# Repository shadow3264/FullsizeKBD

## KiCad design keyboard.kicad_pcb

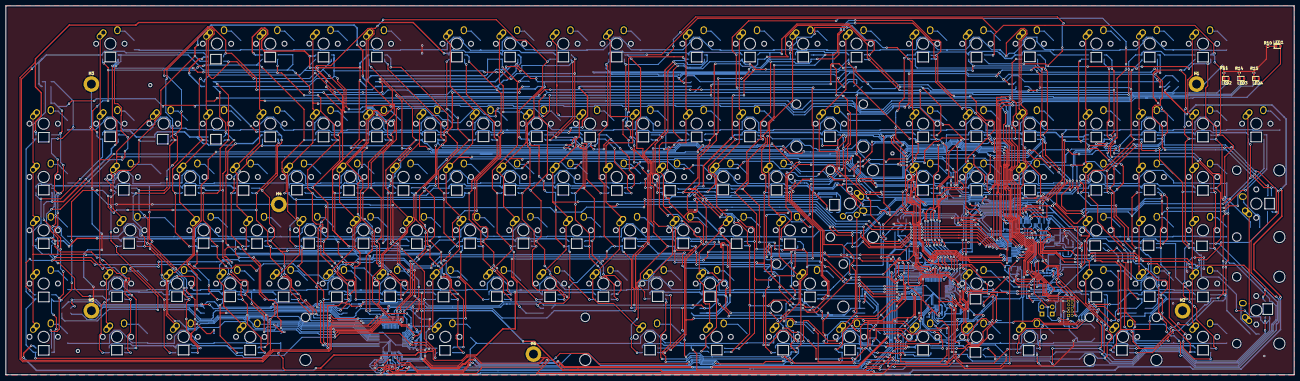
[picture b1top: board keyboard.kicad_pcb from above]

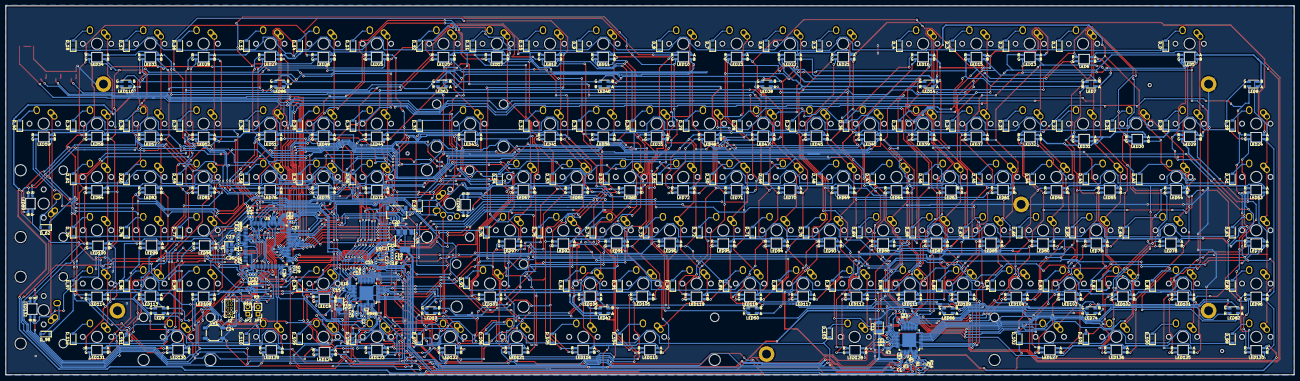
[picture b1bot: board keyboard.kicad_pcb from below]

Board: 2 copper layers, 460.4 x 131.8 mm, 434 parts (307 on the bottom side), 233 nets.

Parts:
C1, C2, C4, C6, C7, C9, C12, C15: 0.47uF; C_0402_1005Metric
C3, C5, C8, C10, C13, C16, C17, C18, C19, C21, C24, C28, C29, C30, C31, C32, C34, C38, C39, C40, C41, C42, C43, C44: 0.1uF; C_0402_1005Metric
C11, C14: 22uF; CP_EIA-3528-21_Kemet-B
C20, C27, C33: 1uF; C_0402_1005Metric
C23, C26: 12pF; C_0402_1005Metric
C25, C36, C37: 4.7uF; C_0402_1005Metric
C35: 10uF; C_0402_1005Metric
D_0, D_1, D_2, D_3, D_4, D_5, D_6, D_7, D_8, D_9, D_10, D_11, D_12, D_13, D_14, D_15, D_16, D_17, D_18, D_19, D_20, D_21, D_22, D_23, D_24, D_25, D_26, D_27, D_28, D_29, D_30, D_31, D_32, D_33, D_34, D_35, D_36, D_37, D_38, D_39, D_40, D_41, D_42, D_43, D_44, D_45, D_46, D_47, D_48, D_49, D_50, D_51, D_52, D_53, D_54, D_55, D_56, D_57, D_58, D_59, D_60, D_61, D_62, D_63, D_64, D_65, D_66, D_67, D_68, D_69, D_70, D_71, D_72, D_73, D_74, D_75, D_76, D_77, D_78, D_79, D_80, D_81, D_82, D_83, D_84, D_85, D_86, D_87, D_88, D_89, D_90, D_91, D_92, D_93, D_94, D_95, D_96, D_97, D_98, D_99, D_100, D_101, D_102, D_103, D_104, D_105, D_106, D_107, D_108, D_109, D_110, D_111, D_112: D; D_SOD-123
H1, H2, H3, H4, H5, H6: MountingHole_Pad; MountingHole_3.2mm_M3_DIN965_Pad
J1: USB; JST_SH_SM05B-SRSS-TB_1x05-1MP_P1.00mm_Horizontal
J2: Conn_02x05_Odd_Even; PinHeader_2x05_P1.27mm_Vertical
JP1, JP2: Jumper; PinHeader_1x02_P2.54mm_Vertical
K_0, K_1, K_2, K_3, K_4, K_5, K_6, K_7, K_8, K_9, K_10, K_11, K_12, K_13, K_14, K_15, K_16, K_17, K_18, K_19, K_20, K_21, K_22, K_23, K_24, K_25, K_26, K_27, K_28, K_29, K_30, K_31, K_32, K_34, K_35, K_36, K_37, K_38, K_39, K_40, K_41, K_43, K_44, K_45, K_46, K_47, K_48, K_49, K_50, K_51, K_52, K_53, K_54, K_56, K_57, K_58, K_59, K_60, K_61, K_63, K_65, K_66, K_67, K_68, K_69, K_70, K_71, K_72, K_73, K_74, K_75, K_76, K_77, K_78, K_79, K_80, K_82, K_83, K_84, K_85, K_86, K_87, K_88, K_89, K_90, K_91, K_92, K_94, K_95, K_96, K_97, K_99, K_108, K_109, K_110, K_112: KEYSW; MX-1U-NoLED
K_33, K_62, K_98, K_111: KEYSW; MX-2U-NoLED
K_42: KEYSW; MX-1.5U-NoLED
K_55: KEYSW; MX-ISO-NoLED
K_64: KEYSW; MX-1.75U-NoLED
K_81, K_100, K_101, K_102, K_104, K_105, K_106, K_107: KEYSW; MX-1.25U-NoLED
K_93: KEYSW; MX-2.75U-NoLED
K_103: KEYSW; MX-6.25U-NoLED
LED1, LED2, LED3, LED4: LED; LED_0603_1608Metric
LED5, LED6, LED10, LED11, LED12, LED13, LED15, LED16, LED17, LED18, LED20, LED21, LED22, LED23, LED24, LED25, LED26, LED27, LED28, LED29, LED30, LED31, LED32, LED33, LED34, LED35, LED36, LED37, LED39, LED40, LED41, LED43, LED44, LED45, LED47, LED48, LED49, LED51, LED52, LED53, LED54, LED55, LED56, LED57, LED58, LED59, LED60, LED61, LED63, LED64, LED65, LED67, LED68, LED69, LED70, LED71, LED72, LED73, LED75, LED76, LED77, LED78, LED79, LED80, LED81, LED83, LED84, LED85, LED87, LED88, LED89, LED90, LED91, LED92, LED93, LED94, LED95, LED96, LED97, LED98, LED99, LED100, LED101, LED102, LED103, LED104, LED105, LED106, LED107, LED108, LED109, LED111, LED112, LED113, LED114, LED115, LED116, LED117, LED118, LED119, LED120, LED121, LED122, LED123, LED124, LED125, LED126, LED127, LED128, LED129, LED130, LED131, LED132: RGBLED; LED_RGB_3.2x2.8_REVMOUNT
LED7, LED8, LED9, LED14, LED19, LED38, LED42, LED46, LED50, LED62, LED66, LED74, LED82, LED86, LED110: RGBLED; LED_RGB_3528
R1, R2, R16: 100k; R_0402_1005Metric
R3, R4: 20k; R_0402_1005Metric
R5, R6, R7, R8, R10, R11, R14, R15: 1k; R_0402_1005Metric
R9, R12: 10k; R_0402_1005Metric
R13: 220; R_0402_1005Metric
SW1: SW_Push; SW_SPST_SKQG_WithStem
U1, U2: IS31FL3733-TQ; TQFP-48-1EP_7x7mm_P0.5mm_EP5x5mm
U3: STM32F411VETx; LQFP-100_14x14mm_P0.5mm
U4: LD1117S50TR_SOT223; SOT-223-3_TabPin2
U5: MIC5504-3.3YM5; SOT-23-5
Y1: 16MHz; Crystal_SMD_3225-4Pin_3.2x2.5mm

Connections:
+3V3: C1.1, C2.2, C28.1, C29.1, C30.1, C31.1, C32.1, C33.1, C34.1, C35.1, C38.1, C39.1, C40.1, C41.1, C42.1, C43.1, C44.1, J2.1, JP1.2, JP2.2, R1.1, R5.1, R6.1, R7.1, R8.1, U1.39, U2.39, U3.6, U3.11, U3.19, U3.28, U3.50, U3.75, U3.100, U5.5
+5V: C3.1, C4.1, C5.1, C6.1, C7.1, C8.1, C9.1, C10.1, C11.1, C12.2, C13.2, C14.1, C15.2, C16.2, C17.1, C18.1, C19.1, C21.1, C25.1, C27.1, U1.20, U1.29, U1.37, U1.38, U2.20, U2.29, U2.37, U2.38, U4.2, U5.1, U5.3
/ledmatrix/LD1_CS1: LED5.1, LED6.1, LED7.1, LED8.1, U1.16
/ledmatrix/LD1_CS2: LED13.1, LED14.1, LED15.1, LED16.1, U1.17
/ledmatrix/LD1_CS3: LED21.1, LED22.1, LED23.1, LED24.1, U1.18
/ledmatrix/LD1_CS4: LED29.1, LED30.1, LED31.1, LED32.1, U1.19
/ledmatrix/LD1_CS5: LED37.1, LED38.1, LED39.1, LED40.1, U1.21
/ledmatrix/LD1_CS6: LED45.1, LED46.1, LED47.1, LED48.1, U1.22
/ledmatrix/LD1_CS7: LED53.1, LED54.1, LED55.1, LED56.1, U1.23
/ledmatrix/LD1_CS8: LED61.1, LED62.1, LED63.1, LED64.1, U1.24
/ledmatrix/LD1_CS9: LED69.1, LED70.1, LED71.1, LED72.1, U1.25
/ledmatrix/LD1_CS10: LED77.1, LED78.1, LED79.1, LED80.1, U1.26
/ledmatrix/LD1_CS11: LED85.1, LED86.1, LED87.1, LED88.1, U1.27
/ledmatrix/LD1_CS12: LED93.1, LED94.1, LED95.1, LED96.1, U1.28
/ledmatrix/LD1_CS13: LED101.1, LED102.1, LED103.1, LED104.1, U1.30
/ledmatrix/LD1_CS14: LED109.1, LED110.1, LED111.1, LED112.1, U1.31
/ledmatrix/LD1_CS15: LED117.1, LED118.1, LED119.1, LED120.1, U1.32
/ledmatrix/LD1_CS16: LED125.1, LED126.1, LED127.1, LED128.1, U1.33
/ledmatrix/LD1_SW1: LED5.3, LED13.3, LED21.3, LED29.3, LED37.3, LED45.3, LED53.3, LED61.3, LED69.3, LED77.3, LED85.3, LED93.3, LED101.3, LED109.3, LED117.3, LED125.3, U1.2
/ledmatrix/LD1_SW2: LED5.2, LED13.2, LED21.2, LED29.2, LED37.2, LED45.2, LED53.2, LED61.2, LED69.2, LED77.2, LED85.2, LED93.2, LED101.2, LED109.2, LED117.2, LED125.2, U1.3
/ledmatrix/LD1_SW3: LED5.4, LED13.4, LED21.4, LED29.4, LED37.4, LED45.4, LED53.4, LED61.4, LED69.4, LED77.4, LED85.4, LED93.4, LED101.4, LED109.4, LED117.4, LED125.4, U1.4
/ledmatrix/LD1_SW4: LED6.3, LED14.3, LED22.3, LED30.3, LED38.3, LED46.3, LED54.3, LED62.3, LED70.3, LED78.3, LED86.3, LED94.3, LED102.3, LED110.3, LED118.3, LED126.3, U1.6
/ledmatrix/LD1_SW5: LED6.2, LED14.2, LED22.2, LED30.2, LED38.2, LED46.2, LED54.2, LED62.2, LED70.2, LED78.2, LED86.2, LED94.2, LED102.2, LED110.2, LED118.2, LED126.2, U1.7
/ledmatrix/LD1_SW6: LED6.4, LED14.4, LED22.4, LED30.4, LED38.4, LED46.4, LED54.4, LED62.4, LED70.4, LED78.4, LED86.4, LED94.4, LED102.4, LED110.4, LED118.4, LED126.4, U1.8
/ledmatrix/LD1_SW7: LED7.3, LED15.3, LED23.3, LED31.3, LED39.3, LED47.3, LED55.3, LED63.3, LED71.3, LED79.3, LED87.3, LED95.3, LED103.3, LED111.3, LED119.3, LED127.3, U1.9
/ledmatrix/LD1_SW8: LED7.2, LED15.2, LED23.2, LED31.2, LED39.2, LED47.2, LED55.2, LED63.2, LED71.2, LED79.2, LED87.2, LED95.2, LED103.2, LED111.2, LED119.2, LED127.2, U1.10
/ledmatrix/LD1_SW9: LED7.4, LED15.4, LED23.4, LED31.4, LED39.4, LED47.4, LED55.4, LED63.4, LED71.4, LED79.4, LED87.4, LED95.4, LED103.4, LED111.4, LED119.4, LED127.4, U1.11
/ledmatrix/LD1_SW10: LED8.3, LED16.3, LED24.3, LED32.3, LED40.3, LED48.3, LED56.3, LED64.3, LED72.3, LED80.3, LED88.3, LED96.3, LED104.3, LED112.3, LED120.3, LED128.3, U1.13
/ledmatrix/LD1_SW11: LED8.2, LED16.2, LED24.2, LED32.2, LED40.2, LED48.2, LED56.2, LED64.2, LED72.2, LED80.2, LED88.2, LED96.2, LED104.2, LED112.2, LED120.2, LED128.2, U1.14
/ledmatrix/LD1_SW12: LED8.4, LED16.4, LED24.4, LED32.4, LED40.4, LED48.4, LED56.4, LED64.4, LED72.4, LED80.4, LED88.4, LED96.4, LED104.4, LED112.4, LED120.4, LED128.4, U1.15
/ledmatrix/LD2_CS1: LED9.1, LED10.1, LED11.1, LED12.1, U2.16
/ledmatrix/LD2_CS2: LED17.1, LED18.1, LED19.1, LED20.1, U2.17
/ledmatrix/LD2_CS3: LED25.1, LED26.1, LED27.1, LED28.1, U2.18
/ledmatrix/LD2_CS4: LED33.1, LED34.1, LED35.1, LED36.1, U2.19
/ledmatrix/LD2_CS5: LED41.1, LED42.1, LED43.1, LED44.1, U2.21
/ledmatrix/LD2_CS6: LED49.1, LED50.1, LED51.1, LED52.1, U2.22
/ledmatrix/LD2_CS7: LED57.1, LED58.1, LED59.1, LED60.1, U2.23
/ledmatrix/LD2_CS8: LED65.1, LED66.1, LED67.1, LED68.1, U2.24
/ledmatrix/LD2_CS9: LED73.1, LED74.1, LED75.1, LED76.1, U2.25
/ledmatrix/LD2_CS10: LED81.1, LED82.1, LED83.1, LED84.1, U2.26
/ledmatrix/LD2_CS11: LED89.1, LED90.1, LED91.1, LED92.1, U2.27
/ledmatrix/LD2_CS12: LED97.1, LED98.1, LED99.1, LED100.1, U2.28
/ledmatrix/LD2_CS13: LED105.1, LED106.1, LED107.1, LED108.1, U2.30
/ledmatrix/LD2_CS14: LED113.1, LED114.1, LED115.1, LED116.1, U2.31
/ledmatrix/LD2_CS15: LED121.1, LED122.1, LED123.1, LED124.1, U2.32
/ledmatrix/LD2_CS16: LED129.1, LED130.1, LED131.1, LED132.1, U2.33
/ledmatrix/LD2_SW1: LED9.3, LED17.3, LED25.3, LED33.3, LED41.3, LED49.3, LED57.3, LED65.3, LED73.3, LED81.3, LED89.3, LED97.3, LED105.3, LED113.3, LED121.3, LED129.3, U2.2
/ledmatrix/LD2_SW2: LED9.2, LED17.2, LED25.2, LED33.2, LED41.2, LED49.2, LED57.2, LED65.2, LED73.2, LED81.2, LED89.2, LED97.2, LED105.2, LED113.2, LED121.2, LED129.2, U2.3
/ledmatrix/LD2_SW3: LED9.4, LED17.4, LED25.4, LED33.4, LED41.4, LED49.4, LED57.4, LED65.4, LED73.4, LED81.4, LED89.4, LED97.4, LED105.4, LED113.4, LED121.4, LED129.4, U2.4
/ledmatrix/LD2_SW4: LED10.3, LED18.3, LED26.3, LED34.3, LED42.3, LED50.3, LED58.3, LED66.3, LED74.3, LED82.3, LED90.3, LED98.3, LED106.3, LED114.3, LED122.3, LED130.3, U2.6
/ledmatrix/LD2_SW5: LED10.2, LED18.2, LED26.2, LED34.2, LED42.2, LED50.2, LED58.2, LED66.2, LED74.2, LED82.2, LED90.2, LED98.2, LED106.2, LED114.2, LED122.2, LED130.2, U2.7
/ledmatrix/LD2_SW6: LED10.4, LED18.4, LED26.4, LED34.4, LED42.4, LED50.4, LED58.4, LED66.4, LED74.4, LED82.4, LED90.4, LED98.4, LED106.4, LED114.4, LED122.4, LED130.4, U2.8
/ledmatrix/LD2_SW7: LED11.3, LED19.3, LED27.3, LED35.3, LED43.3, LED51.3, LED59.3, LED67.3, LED75.3, LED83.3, LED91.3, LED99.3, LED107.3, LED115.3, LED123.3, LED131.3, U2.9
/ledmatrix/LD2_SW8: LED11.2, LED19.2, LED27.2, LED35.2, LED43.2, LED51.2, LED59.2, LED67.2, LED75.2, LED83.2, LED91.2, LED99.2, LED107.2, LED115.2, LED123.2, LED131.2, U2.10
/ledmatrix/LD2_SW9: LED11.4, LED19.4, LED27.4, LED35.4, LED43.4, LED51.4, LED59.4, LED67.4, LED75.4, LED83.4, LED91.4, LED99.4, LED107.4, LED115.4, LED123.4, LED131.4, U2.11
/ledmatrix/LD2_SW10: LED12.3, LED20.3, LED28.3, LED36.3, LED44.3, LED52.3, LED60.3, LED68.3, LED76.3, LED84.3, LED92.3, LED100.3, LED108.3, LED116.3, LED124.3, LED132.3, U2.13
/ledmatrix/LD2_SW11: LED12.2, LED20.2, LED28.2, LED36.2, LED44.2, LED52.2, LED60.2, LED68.2, LED76.2, LED84.2, LED92.2, LED100.2, LED108.2, LED116.2, LED124.2, LED132.2, U2.14
/ledmatrix/LD2_SW12: LED12.4, LED20.4, LED28.4, LED36.4, LED44.4, LED52.4, LED60.4, LED68.4, LED76.4, LED84.4, LED92.4, LED100.4, LED108.4, LED116.4, LED124.4, LED132.4, U2.15
/mcu/SYNC: U1.40, U2.40
BOOT0: JP1.1, R9.2, U3.94
BOOT1: JP2.1, R12.2, U3.37
GND: C1.2, C2.1, C3.2, C4.2, C5.2, C6.2, C7.2, C8.2, C9.2, C10.2, C11.2, C12.1, C13.1, C14.2, C15.1, C16.1, C17.2, C18.2, C19.2, C20.2, C21.2, C23.2, C24.2, C25.2, C26.2, C27.2, C28.2, C29.2, C30.2, C31.2, C32.2, C33.2, C34.2, C35.2, C36.2, C37.2, C38.2, C39.2, C40.2, C41.2, C42.2, C43.2, C44.2, H1.1, H2.1, H3.1, H4.1, H5.1, H6.1, J1.1, J2.3, J2.5, J2.9, R2.2, R3.2, R4.2, R9.1, R10.1, R11.1, R12.1, R14.1, R15.1, R16.2, SW1.2, U1.5, U1.12, U1.34, U1.43, U1.44, U1.48, U1.49, U2.5, U2.12, U2.34, U2.43, U2.44, U2.48, U2.49, U3.10, U3.20, U3.27, U3.49, U3.74, U3.99, U4.1, U5.2, Y1.2, Y1.4
HSE_IN: C23.1, U3.12, Y1.1
HSE_OUT: R13.1, U3.13
I2C1_SCL: R5.2, U1.42, U3.92
I2C1_SDA: R7.2, U1.41, U3.93
I2C2_SCL: R6.2, U2.42, U3.47
I2C2_SDA: R8.2, U2.41, U3.96
IICRST: R16.1, U1.47, U2.47
INTB: R1.2, U1.45
NRST: C24.1, J2.10, SW1.1, U3.14
unnamed: C26.1, R13.2, Y1.3
unnamed: C36.1, U3.48
unnamed: C37.1, U3.73
unnamed: D_0.2, K_0.2
unnamed: D_1.2, K_1.2
unnamed: D_2.2, K_2.2
unnamed: D_3.2, K_3.2
unnamed: D_4.2, K_4.2
unnamed: D_5.2, K_5.2
unnamed: D_6.2, K_6.2
unnamed: D_7.2, K_7.2
unnamed: D_8.2, K_8.2
unnamed: D_9.2, K_9.2
unnamed: D_10.2, K_10.2
unnamed: D_11.2, K_11.2
unnamed: D_12.2, K_12.2
unnamed: D_13.2, K_13.2
unnamed: D_14.2, K_14.2
unnamed: D_15.2, K_15.2
unnamed: D_16.2, K_16.2
unnamed: D_17.2, K_17.2
unnamed: D_18.2, K_18.2
unnamed: D_19.2, K_19.2
unnamed: D_20.2, K_20.2
unnamed: D_21.2, K_21.2
unnamed: D_22.2, K_22.2
unnamed: D_23.2, K_23.2
unnamed: D_24.2, K_24.2
unnamed: D_25.2, K_25.2
unnamed: D_26.2, K_26.2
unnamed: D_27.2, K_27.2
unnamed: D_28.2, K_28.2
unnamed: D_29.2, K_29.2
unnamed: D_30.2, K_30.2
unnamed: D_31.2, K_31.2
unnamed: D_32.2, K_32.2
unnamed: D_33.2, K_33.2
unnamed: D_34.2, K_34.2
unnamed: D_35.2, K_35.2
unnamed: D_36.2, K_36.2
unnamed: D_37.2, K_37.2
unnamed: D_38.2, K_38.2
unnamed: D_39.2, K_39.2
unnamed: D_40.2, K_40.2
unnamed: D_41.2, K_41.2
unnamed: D_42.2, K_42.2
unnamed: D_43.2, K_43.2
unnamed: D_44.2, K_44.2
unnamed: D_45.2, K_45.2
unnamed: D_46.2, K_46.2
unnamed: D_47.2, K_47.2
unnamed: D_48.2, K_48.2
unnamed: D_49.2, K_49.2
unnamed: D_50.2, K_50.2
unnamed: D_51.2, K_51.2
unnamed: D_52.2, K_52.2
unnamed: D_53.2, K_53.2
unnamed: D_54.2, K_54.2
unnamed: D_55.2, K_55.2
unnamed: D_56.2, K_56.2
unnamed: D_57.2, K_57.2
unnamed: D_58.2, K_58.2
unnamed: D_59.2, K_59.2
unnamed: D_60.2, K_60.2
unnamed: D_61.2, K_61.2
unnamed: D_62.2, K_62.2
unnamed: D_63.2, K_63.2
unnamed: D_64.2, K_64.2
unnamed: D_65.2, K_65.2
unnamed: D_66.2, K_66.2
unnamed: D_67.2, K_67.2
unnamed: D_68.2, K_68.2
unnamed: D_69.2, K_69.2
unnamed: D_70.2, K_70.2
unnamed: D_71.2, K_71.2
unnamed: D_72.2, K_72.2
unnamed: D_73.2, K_73.2
unnamed: D_74.2, K_74.2
unnamed: D_75.2, K_75.2
unnamed: D_76.2, K_76.2
unnamed: D_77.2, K_77.2
unnamed: D_78.2, K_78.2
unnamed: D_79.2, K_79.2
unnamed: D_80.2, K_80.2
unnamed: D_81.2, K_81.2
unnamed: D_82.2, K_82.2
unnamed: D_83.2, K_83.2
unnamed: D_84.2, K_84.2
unnamed: D_85.2, K_85.2
unnamed: D_86.2, K_86.2
unnamed: D_87.2, K_87.2
unnamed: D_88.2, K_88.2
unnamed: D_89.2, K_89.2
unnamed: D_90.2, K_90.2
unnamed: D_91.2, K_91.2
unnamed: D_92.2, K_92.2
unnamed: D_93.2, K_93.2
unnamed: D_94.2, K_94.2
unnamed: D_95.2, K_95.2
unnamed: D_96.2, K_96.2
unnamed: D_97.2, K_97.2
unnamed: D_98.2, K_98.2
unnamed: D_99.2, K_99.2
unnamed: D_100.2, K_100.2
unnamed: D_101.2, K_101.2
unnamed: D_102.2, K_102.2
unnamed: D_103.2, K_103.2
unnamed: D_104.2, K_104.2
unnamed: D_105.2, K_105.2
unnamed: D_106.2, K_106.2
unnamed: D_107.2, K_107.2
unnamed: D_108.2, K_108.2
unnamed: D_109.2, K_109.2
unnamed: D_110.2, K_110.2
unnamed: D_111.2, K_111.2
unnamed: D_112.2, K_112.2
unnamed: LED1.1, R10.2
unnamed: LED2.1, R11.2
unnamed: LED3.1, R14.2
unnamed: LED4.1, R15.2
unnamed: R3.1, U1.35
unnamed: R4.1, U2.35
PA8: LED2.2, U3.67
PA9: LED3.2, U3.68
PA10: LED4.2, U3.69
PB12: LED1.2, U3.51
SDB: R2.1, U1.46, U2.46, U3.81
SWCLK: J2.4, U3.76
SWDIO: J2.2, U3.72
SWO: J2.6, U3.89
USB_DM: J1.3, U3.70
USB_DP: J1.2, U3.71
VBUS: C20.1, J1.4, U4.3
col0: K_19.1, K_41.1, K_63.1, K_80.1, K_99.1, U3.52
col1: K_0.1, K_20.1, K_81.1, K_100.1, U3.53
col2: K_21.1, K_42.1, K_64.1, U3.54
col3: K_1.1, K_22.1, K_43.1, K_65.1, K_82.1, K_101.1, U3.55
col4: K_2.1, K_23.1, K_44.1, K_66.1, K_83.1, K_102.1, U3.56
col5: K_3.1, K_24.1, K_45.1, K_67.1, K_84.1, U3.57
col6: K_4.1, K_25.1, K_46.1, K_68.1, K_85.1, U3.58
col7: K_26.1, K_47.1, K_69.1, K_86.1, U3.59
col8: K_5.1, K_27.1, K_48.1, K_70.1, K_87.1, K_103.1, U3.60
col9: K_6.1, K_28.1, K_49.1, K_71.1, K_88.1, U3.61
col10: K_7.1, K_29.1, K_50.1, K_72.1, K_89.1, U3.62
col11: K_8.1, K_30.1, K_51.1, K_73.1, K_90.1, K_104.1, U3.63
col12: K_9.1, K_31.1, K_52.1, K_74.1, K_91.1, U3.64
col13: K_10.1, K_32.1, K_53.1, K_75.1, K_92.1, K_105.1, U3.65
col14: K_11.1, K_54.1, K_76.1, K_93.1, K_106.1, U3.66
col15: K_12.1, K_33.1, K_55.1, K_107.1, U3.78
col16: K_13.1, K_34.1, K_56.1, K_108.1, U3.79
col17: K_14.1, K_35.1, K_57.1, K_94.1, K_109.1, U3.80
col18: K_15.1, K_36.1, K_58.1, K_110.1, U3.7
col19: K_16.1, K_37.1, K_59.1, K_77.1, K_95.1, K_111.1, U3.8
col20: K_17.1, K_38.1, K_60.1, K_78.1, K_96.1, U3.9
col21: K_18.1, K_39.1, K_61.1, K_79.1, K_97.1, K_112.1, U3.90
col22: K_40.1, K_62.1, K_98.1, U3.91
row0: D_0.1, D_1.1, D_2.1, D_3.1, D_4.1, D_5.1, D_6.1, D_7.1, D_8.1, D_9.1, D_10.1, D_11.1, D_12.1, D_13.1, D_14.1, D_15.1, D_16.1, D_17.1, D_18.1, U3.82
row1: D_19.1, D_20.1, D_21.1, D_22.1, D_23.1, D_24.1, D_25.1, D_26.1, D_27.1, D_28.1, D_29.1, D_30.1, D_31.1, D_32.1, D_33.1, D_34.1, D_35.1, D_36.1, D_37.1, D_38.1, D_39.1, D_40.1, U3.83
row2: D_41.1, D_42.1, D_43.1, D_44.1, D_45.1, D_46.1, D_47.1, D_48.1, D_49.1, D_50.1, D_51.1, D_52.1, D_53.1, D_54.1, D_55.1, D_56.1, D_57.1, D_58.1, D_59.1, D_60.1, D_61.1, D_62.1, U3.84
row3: D_63.1, D_64.1, D_65.1, D_66.1, D_67.1, D_68.1, D_69.1, D_70.1, D_71.1, D_72.1, D_73.1, D_74.1, D_75.1, D_76.1, D_77.1, D_78.1, D_79.1, U3.85
row4: D_80.1, D_81.1, D_82.1, D_83.1, D_84.1, D_85.1, D_86.1, D_87.1, D_88.1, D_89.1, D_90.1, D_91.1, D_92.1, D_93.1, D_94.1, D_95.1, D_96.1, D_97.1, D_98.1, U3.86
row5: D_99.1, D_100.1, D_101.1, D_102.1, D_103.1, D_104.1, D_105.1, D_106.1, D_107.1, D_108.1, D_109.1, D_110.1, D_111.1, D_112.1, U3.87

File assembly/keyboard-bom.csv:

Comment,Designator,Footprint,LCSC
"22uF","C11,C14","Capacitor_Tantalum_SMD:CP_EIA-3528-21_Kemet-B","C129568"
"0.1uF","C3,C5,C8,C10,C13,C16,C17,C18,C19,C21,C24,C28,C29,C30,C31,C32,C34,C38,C39,C40,C41,C42,C43,C44","Capacitor_SMD:C_0402_1005Metric","C1525"
"4.7uF","C25,C36,C37","Capacitor_SMD:C_0402_1005Metric","C47339"
"12pF","C23,C26","Capacitor_SMD:C_0402_1005Metric","C1547"
"1uF","C20,C27,C33","Capacitor_SMD:C_0402_1005Metric","C52923"
"10uF","C35","Capacitor_SMD:C_0402_1005Metric","C15525"
"0.47uF","C1,C2,C4,C6,C7,C9,C12,C15","Capacitor_SMD:C_0402_1005Metric","C32949"
"D","D_0,D_1,D_2,D_3,D_4,D_5,D_6,D_7,D_8,D_9,D_10,D_11,D_12,D_13,D_14,D_15,D_16,D_17,D_18,D_19,D_20,D_21,D_22,D_23,D_24,D_25,D_26,D_27,D_28,D_29,D_30,D_31,D_32,D_33,D_34,D_35,D_36,D_37,D_38,D_39,D_40,D_41,D_42,D_43,D_44,D_45,D_46,D_47,D_48,D_49,D_50,D_51,D_52,D_53,D_54,D_55,D_56,D_57,D_58,D_59,D_60,D_61,D_62,D_63,D_64,D_65,D_66,D_67,D_68,D_69,D_70,D_71,D_72,D_73,D_74,D_75,D_76,D_77,D_78,D_79,D_80,D_81,D_82,D_83,D_84,D_85,D_86,D_87,D_88,D_89,D_90,D_91,D_92,D_93,D_94,D_95,D_96,D_97,D_98,D_99,D_100,D_101,D_102,D_103,D_104,D_105,D_106,D_107,D_108,D_109,D_110,D_111,D_112","Diode_SMD:D_SOD-123","C81598"
"MountingHole_Pad","H1,H2,H3,H4,H5,H6","MountingHole:MountingHole_3.2mm_M3_DIN965_Pad",""
"USB","J1","Connector_JST:JST_SH_SM05B-SRSS-TB_1x05-1MP_P1.00mm_Horizontal","C265104"
"Conn_02x05_Odd_Even","J2","Connector_PinHeader_1.27mm:PinHeader_2x05_P1.27mm_Vertical",""
"Jumper","JP1,JP2","Connector_PinHeader_2.54mm:PinHeader_1x02_P2.54mm_Vertical",""
"KEYSW","K_0,K_1,K_2,K_3,K_4,K_5,K_6,K_7,K_8,K_9,K_10,K_11,K_12,K_13,K_14,K_15,K_16,K_17,K_18,K_19,K_20,K_21,K_22,K_23,K_24,K_25,K_26,K_27,K_28,K_29,K_30,K_31,K_32,K_34,K_35,K_36,K_37,K_38,K_39,K_40,K_41,K_43,K_44,K_45,K_46,K_47,K_48,K_49,K_50,K_51,K_52,K_53,K_54,K_56,K_57,K_58,K_59,K_60,K_61,K_63,K_65,K_66,K_67,K_68,K_69,K_70,K_71,K_72,K_73,K_74,K_75,K_76,K_77,K_78,K_79,K_80,K_82,K_83,K_84,K_85,K_86,K_87,K_88,K_89,K_90,K_91,K_92,K_94,K_95,K_96,K_97,K_99,K_108,K_109,K_110,K_112","MX_Alps_Hybrid:MX-1U-NoLED",""
"KEYSW","K_103","MX_Alps_Hybrid:MX-6.25U-NoLED",""
"KEYSW","K_33,K_62,K_98,K_111","MX_Alps_Hybrid:MX-2U-NoLED",""
"KEYSW","K_42","MX_Alps_Hybrid:MX-1.5U-NoLED",""
"KEYSW","K_55","FullsizeKBD:MX-ISO-NoLED",""
"KEYSW","K_64","MX_Alps_Hybrid:MX-1.75U-NoLED",""
"KEYSW","K_81,K_100,K_101,K_102,K_104,K_105,K_106,K_107","MX_Alps_Hybrid:MX-1.25U-NoLED",""
"KEYSW","K_93","MX_Alps_Hybrid:MX-2.75U-NoLED",""
"LED","LED1,LED2,LED3,LED4","LED_SMD:LED_0603_1608Metric","C84269"
"RGBLED","LED5,LED6,LED10,LED11,LED12,LED13,LED15,LED16,LED17,LED18,LED20,LED21,LED22,LED23,LED24,LED25,LED26,LED27,LED28,LED29,LED30,LED31,LED32,LED33,LED34,LED35,LED36,LED37,LED39,LED40,LED41,LED43,LED44,LED45,LED47,LED48,LED49,LED51,LED52,LED53,LED54,LED55,LED56,LED57,LED58,LED59,LED60,LED61,LED63,LED64,LED65,LED67,LED68,LED69,LED70,LED71,LED72,LED73,LED75,LED76,LED77,LED78,LED79,LED80,LED81,LED83,LED84,LED85,LED87,LED88,LED89,LED90,LED91,LED92,LED93,LED94,LED95,LED96,LED97,LED98,LED99,LED100,LED101,LED102,LED103,LED104,LED105,LED106,LED107,LED108,LED109,LED111,LED112,LED113,LED114,LED115,LED116,LED117,LED118,LED119,LED120,LED121,LED122,LED123,LED124,LED125,LED126,LED127,LED128,LED129,LED130,LED131,LED132","FullsizeKBD:LED_RGB_3.2x2.8_REVMOUNT",""
"RGBLED","LED7,LED8,LED9,LED14,LED19,LED38,LED42,LED46,LED50,LED62,LED66,LED74,LED82,LED86,LED110","FullsizeKBD:LED_RGB_3528",""
"100k","R1,R2,R16","Resistor_SMD:R_0402_1005Metric","C25741"
"1k","R5,R6,R7,R8,R10,R11,R14,R15","Resistor_SMD:R_0402_1005Metric","C11702"
"220","R13","Resistor_SMD:R_0402_1005Metric","C25091"
"20k","R3,R4","Resistor_SMD:R_0402_1005Metric","C25765"
"10k","R9,R12","Resistor_SMD:R_0402_1005Metric","C25744"
"SW_Push","SW1","Button_Switch_SMD:SW_SPST_SKQG_WithStem","C528026"
"IS31FL3733-TQ","U1,U2","Package_QFP:TQFP-48-1EP_7x7mm_P0.5mm_EP5x5mm","C2678773"
"STM32F411VETx","U3","Package_QFP:LQFP-100_14x14mm_P0.5mm","C382005"
"LD1117S50TR_SOT223","U4","Package_TO_SOT_SMD:SOT-223-3_TabPin2","C134077"
"MIC5504-3.3YM5","U5","Package_TO_SOT_SMD:SOT-23-5","C88419"
"16MHz","Y1","Crystal:Crystal_SMD_3225-4Pin_3.2x2.5mm","C255909"
